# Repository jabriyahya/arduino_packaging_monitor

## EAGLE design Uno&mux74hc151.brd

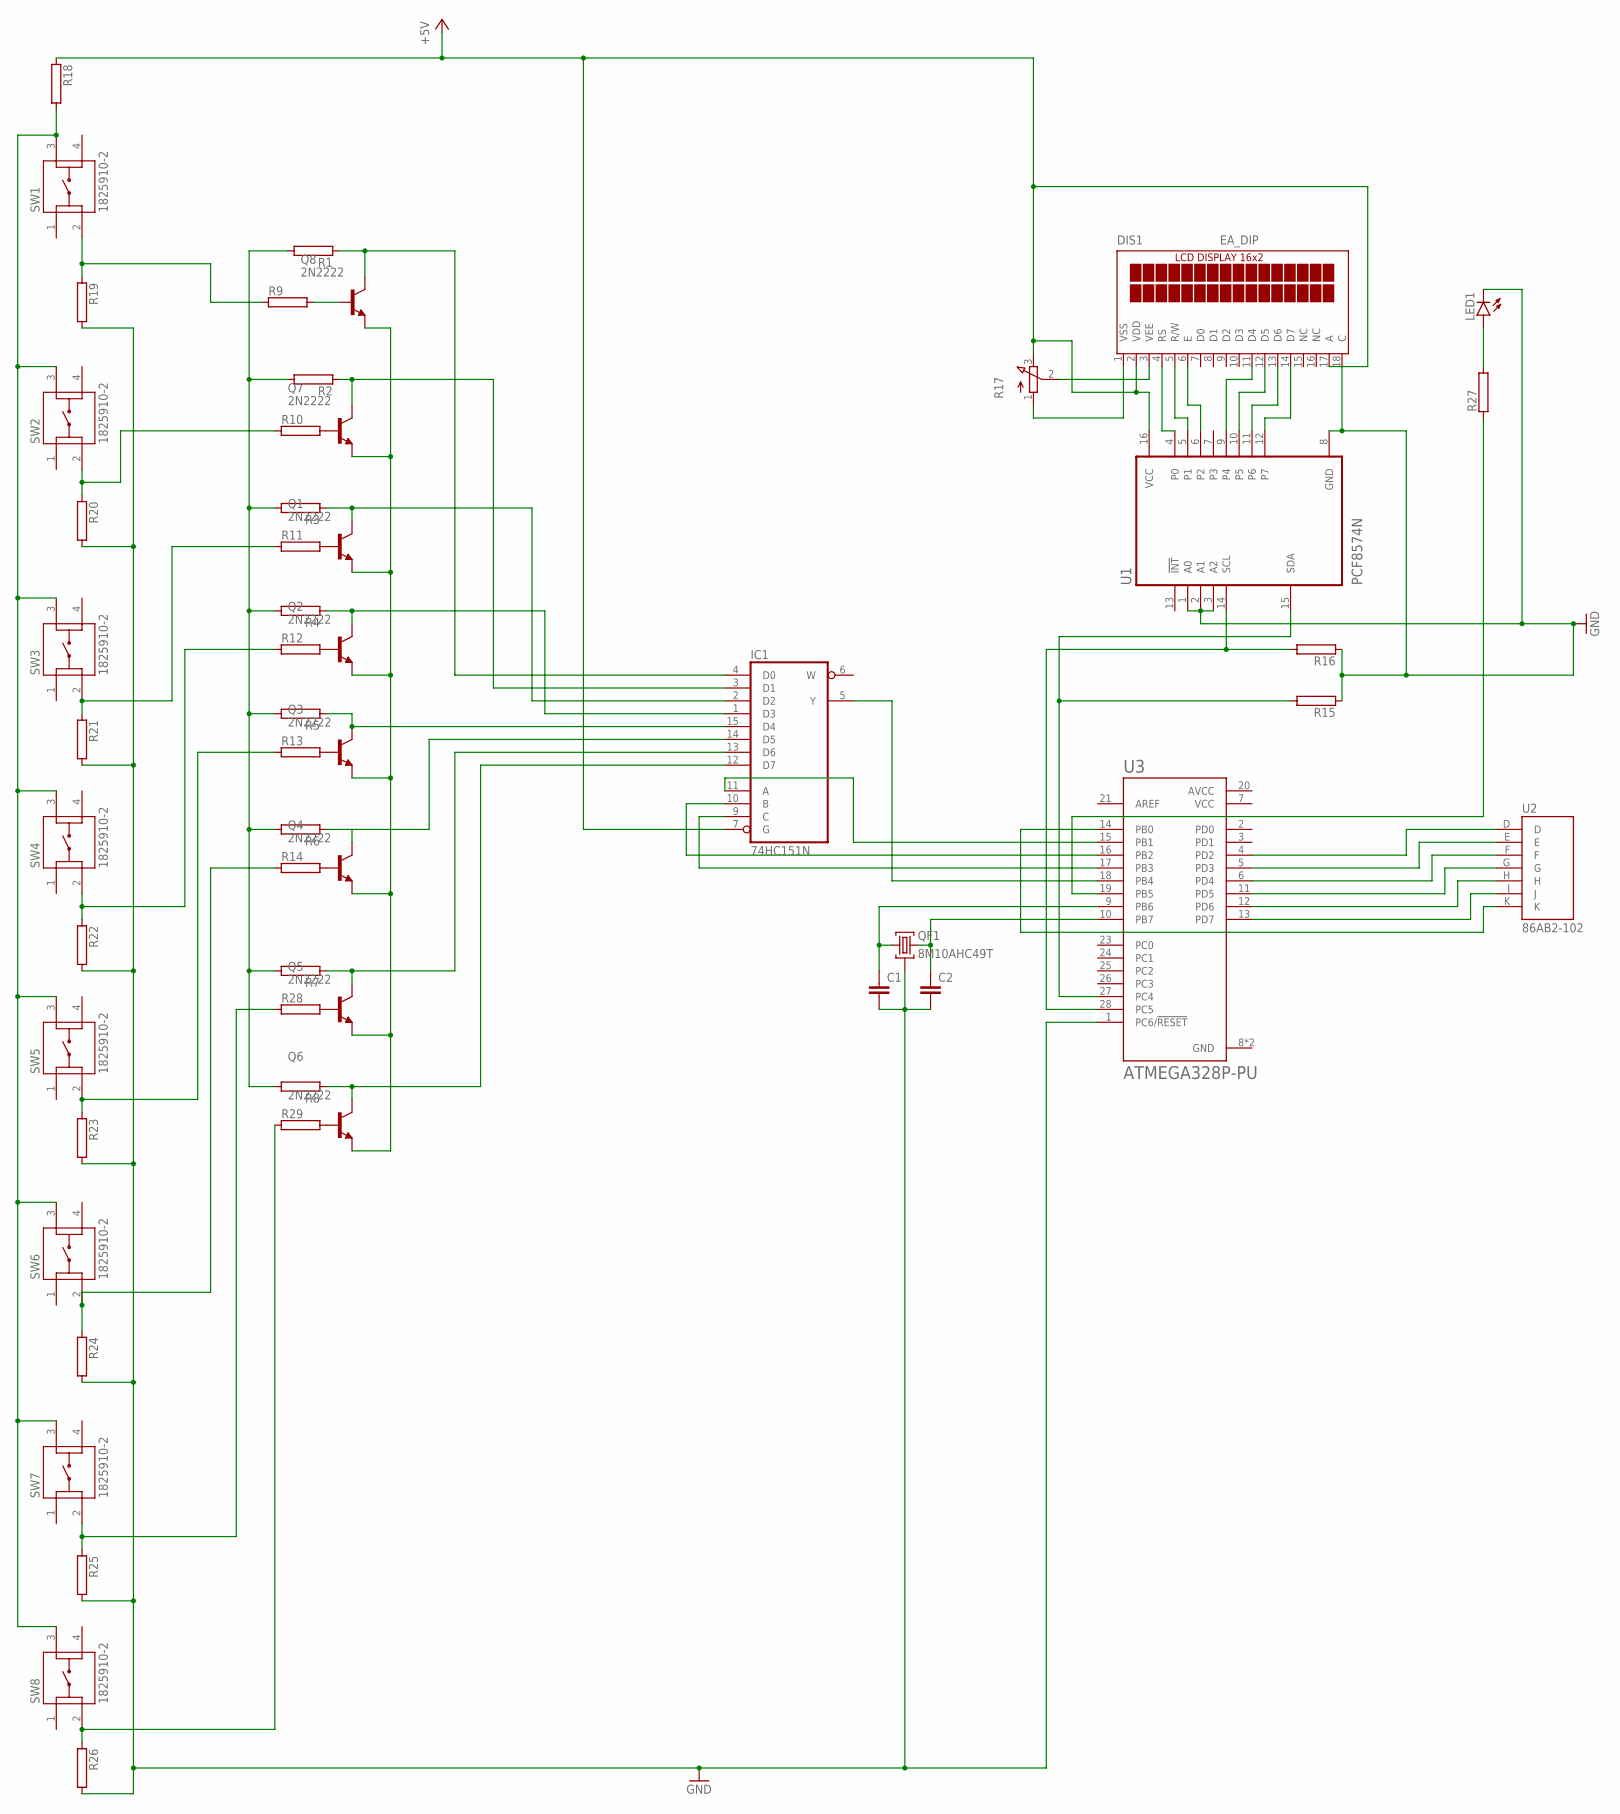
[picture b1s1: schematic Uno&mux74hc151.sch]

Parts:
C1, C2: C2.5/2; C2.5-2
DIS1: EA_DIP
IC1: 74HC151N; DIL16
LED1: LEDB153; Q62902-B153
Q1, Q2, Q3, Q4, Q5, Q6, Q7, Q8: 2N2222; TO18
QF1: 8M10AHC49T; HC49U
R1, R2, R3, R4, R5, R6, R7, R8, R9, R10, R11, R12, R13, R14, R15, R16, R18, R19, R20, R21, R22, R23, R24, R25, R26, R27, R28, R29: RAC01; AC01
R17: 3RP/1610N
SW1, SW2, SW3, SW4, SW5, SW6, SW7, SW8: 1825910-2; TE_1825910-2
U1: PCF8574N; DIP794W45P254L1969H508Q16
U2: 86AB2-102; KEYPAD_86AB2-102
U3: ATMEGA328P-PU; DIP794W46P254L2967H457Q28B

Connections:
+5V: DIS1.2 (VDD), DIS1.17 (A), IC1.7 (G), R17.3 (E), R18.1, U1.16 (VCC)
AVCC: U3.20 (AVCC)
GND: C1.2, C2.2, DIS1.18 (C), IC1.8 (GND), LED1.K (C), QF1.2, R15.1, R16.1, R19.2, R20.2, R21.2, R22.2, R23.2, R24.2, R25.2, R26.2, U1.1 (A0), U1.2 (A1), U1.3 (A2), U1.8 (GND), U3.1 (PC6/!RESET), U3.8 (GND), U3.22 (GND)
unnamed: R16.2, U1.14 (SCL), U3.28 (PC5)
unnamed: R15.2, U1.15 (SDA), U3.27 (PC4)
unnamed: U2.D, U3.4 (PD2)
unnamed: U2.E, U3.5 (PD3)
unnamed: U2.F, U3.6 (PD4)
unnamed: U2.G, U3.11 (PD5)
unnamed: DIS1.14 (D7), U1.12 (P7)
unnamed: DIS1.13 (D6), U1.11 (P6)
unnamed: DIS1.11 (D4), U1.9 (P4)
unnamed: DIS1.12 (D5), U1.10 (P5)
unnamed: DIS1.6 (E), U1.6 (P2)
unnamed: DIS1.5 (R/W), U1.5 (P1)
unnamed: DIS1.4 (RS), U1.4 (P0)
unnamed: LED1.A, R27.2
unnamed: IC1.5 (Y), U3.18 (PB4)
unnamed: R10.1, R20.1, SW2.2
unnamed: IC1.3 (D1), Q7.3 (C), R2.1
unnamed: IC1.2 (D2), Q1.3 (C), R3.1
unnamed: IC1.1 (D3), Q2.3 (C), R4.1
unnamed: IC1.15 (D4), Q3.3 (C), R5.1
unnamed: IC1.14 (D5), Q4.3 (C), R6.1
unnamed: IC1.13 (D6), Q5.3 (C), R7.1
unnamed: IC1.12 (D7), Q6.3 (C), R8.1
unnamed: Q6.2 (B), R29.2
unnamed: Q5.2 (B), R28.2
unnamed: Q4.2 (B), R14.2
unnamed: Q3.2 (B), R13.2
unnamed: Q2.2 (B), R12.2
unnamed: Q1.2 (B), R11.2
unnamed: Q7.2 (B), R10.2
unnamed: Q8.2 (B), R9.2
unnamed: R1.2, R2.2, R3.2, R4.2, R5.2, R6.2, R7.2, R8.2
unnamed: R9.1, R19.1, SW1.2
unnamed: R12.1, R22.1, SW4.2
unnamed: R13.1, R23.1, SW5.2
unnamed: R14.1, R24.1, SW6.2
unnamed: R25.1, R28.1, SW7.2
unnamed: C2.1, QF1.3, U3.10 (PB7)
unnamed: C1.1, QF1.1, U3.9 (PB6)
unnamed: Q1.1 (E), Q2.1 (E), Q3.1 (E), Q4.1 (E), Q5.1 (E), Q6.1 (E), Q7.1 (E), Q8.1 (E)
unnamed: IC1.4 (D0), Q8.3 (C), R1.1
unnamed: IC1.11 (A), U3.15 (PB1)
unnamed: R18.2, SW1.3, SW2.3, SW3.3, SW4.3, SW5.3, SW6.3, SW7.3, SW8.3
unnamed: U2.H, U3.12 (PD6)
unnamed: U2.J, U3.13 (PD7)
unnamed: IC1.10 (B), U3.16 (PB2)
unnamed: U2.K, U3.14 (PB0)
unnamed: IC1.9 (C), U3.17 (PB3)
unnamed: R11.1, R21.1, SW3.2
unnamed: DIS1.1 (VSS), R17.1 (A)
unnamed: DIS1.3 (VEE), R17.2 (S)
unnamed: R27.1, U3.19 (PB5)
unnamed: R26.1, R29.1, SW8.2
VCC: IC1.16 (VCC), U3.7 (VCC)

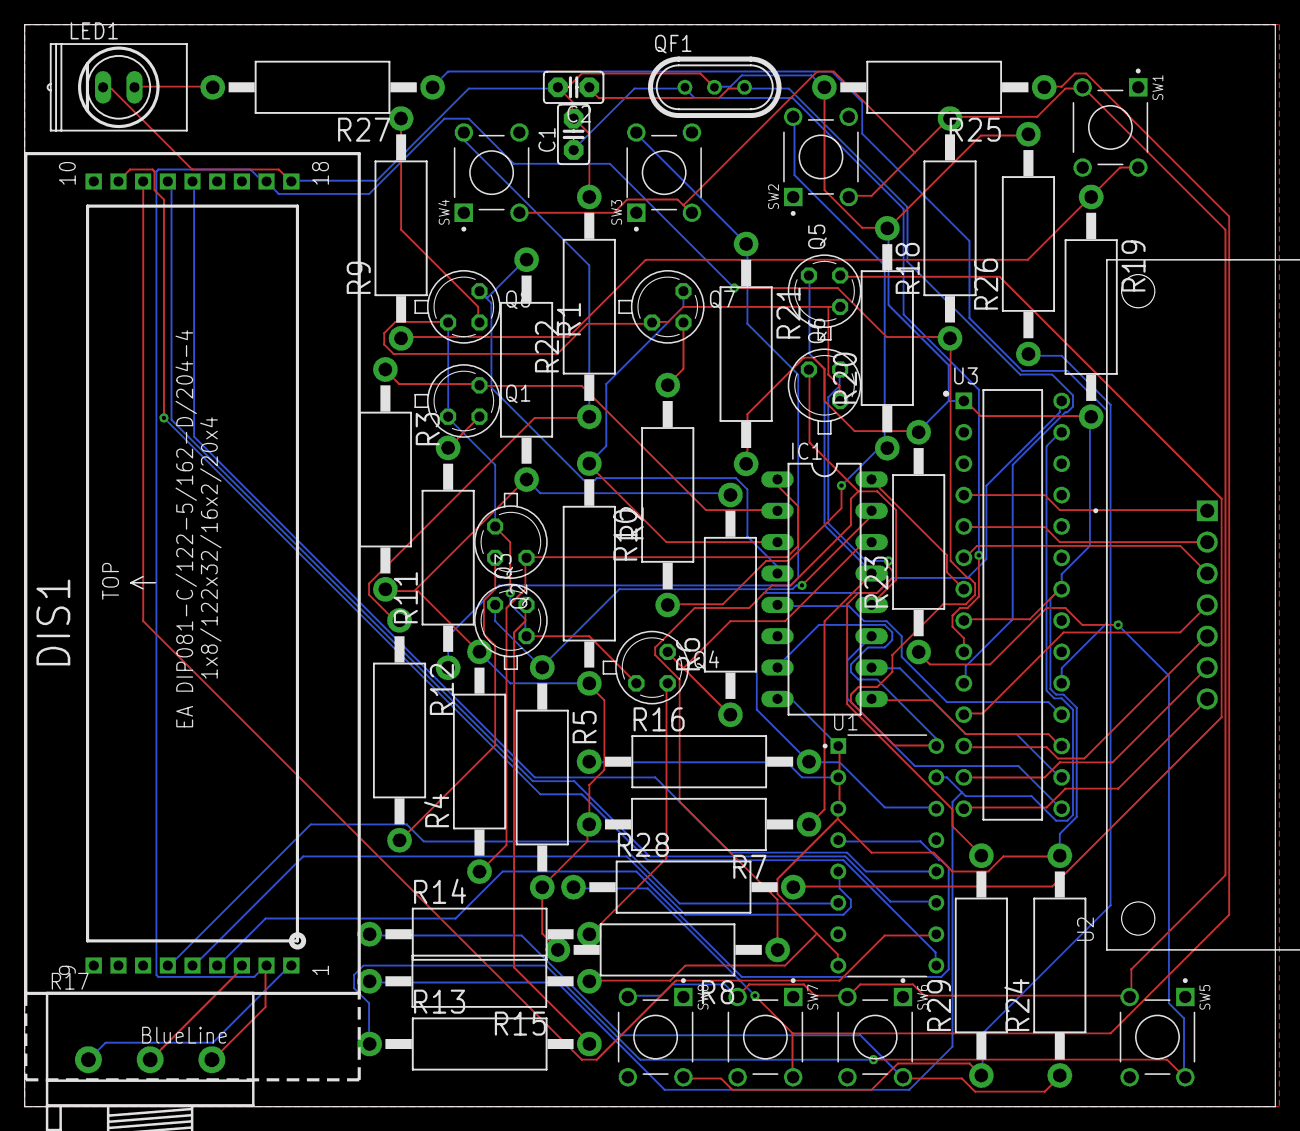
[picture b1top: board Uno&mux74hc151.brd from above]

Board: 2 copper layers, 101.3 x 87.6 mm, 54 parts (0 on the bottom side), 56 nets.
